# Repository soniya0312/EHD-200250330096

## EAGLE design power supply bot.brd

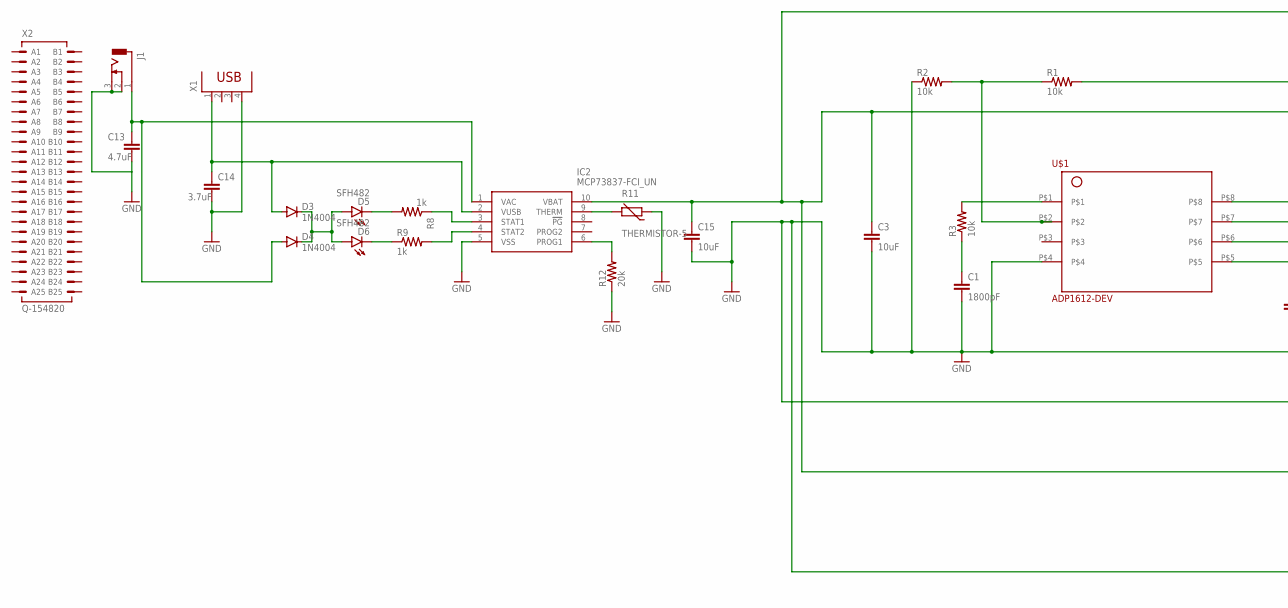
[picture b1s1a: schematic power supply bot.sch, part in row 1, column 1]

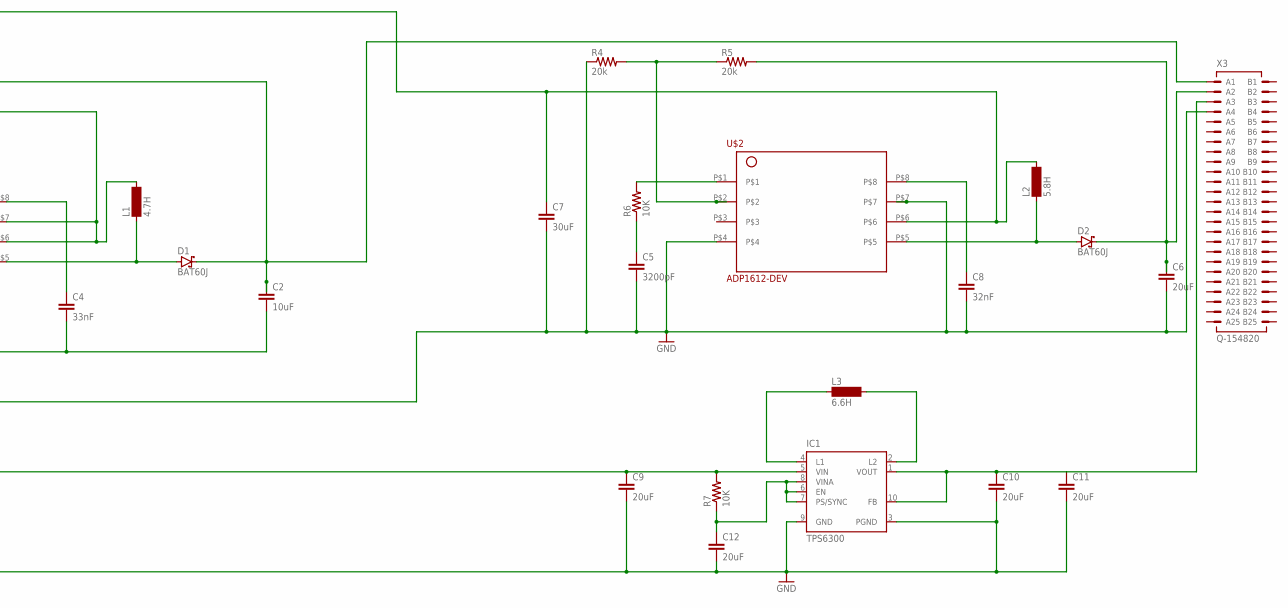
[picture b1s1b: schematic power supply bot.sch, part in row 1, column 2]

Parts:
C1: 1800pF; C2.5-4
C2, C3: 10uF; C2.5-4
C4: 33nF; C2.5-4
C5: 3200pF; C2.5-4
C6: 20uF; C2.5-4
C7: 30uF; C2.5-4
C8: 32nF; C2.5-4
C9, C10, C11, C12: 20uF; C2.5-3
C13: 4.7uF; C2.5-3
C14: 3.7uF; C2.5-3
C15: 10uF; C2.5-3
D1, D2: BAT60J; SOD323_ST
D3, D4: 1N4004; DO41-10
D5, D6: SFH482
IC1: TPS6300; DRC-S-PVSON-N10
IC2: MCP73837-FCI_UN; SOP50P490X110-10N
J1: DCJ0303
L1: 4.7H; BS11
L2: 5.8H; BS11
L3: 6.6H; BS75
R1, R2, R3: 10k; 0204/7
R4, R5: 20k; 0204/7
R6: 10K; 0204/7
R7: 10K; 0204/5
R8, R9: 1k; 0204/5
R11: THERMISTOR-5; R-5
R12: 20k; 0204/5
U$1, U$2: ADP1612-DEV; TQFP-ADP1612
X1: PN61729
X2, X3: Q-154820; 154820

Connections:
GND: C1.2, C2.2, C3.2, C4.2, C5.2, C6.2, C7.2, C8.2, C9.2, C10.2, C11.2, C12.2, C13.2, C14.1, C14.2, C15.2, D3.A, IC1.3 (PGND), IC1.9 (GND), IC2.2 (VUSB), IC2.5 (VSS), J1.2, J1.3, R2.1, R4.1, R11.1, R12.1, U$1.P$4, U$2.P$4, U$2.P$7, X1.1, X1.4, X3.A4
unnamed: R3.2, U$1.P$1
unnamed: C1.1, R3.1
unnamed: R1.1, R2.2, U$1.P$2
unnamed: C2.1, D1.C, R1.2, X3.A1
unnamed: D1.A, L1.1, U$1.P$5
unnamed: C4.1, U$1.P$8
unnamed: C3.1, C7.1, C9.1, C15.1, IC1.5 (VIN), IC2.10 (VBAT), L1.2, L2.2, R7.2, U$1.P$6, U$1.P$7, U$2.P$6
unnamed: R6.2, U$2.P$1
unnamed: C5.1, R6.1
unnamed: R4.2, R5.1, U$2.P$2
unnamed: C6.1, D2.C, R5.2, X3.A2
unnamed: C8.1, U$2.P$8
unnamed: D2.A, L2.1, U$2.P$5
unnamed: IC1.4 (L1), L3.1
unnamed: IC1.2 (L2), L3.2
unnamed: C10.1, C11.1, IC1.1 (VOUT), IC1.10 (FB), X3.A3
unnamed: IC2.9 (THERM), R11.2
unnamed: C12.1, IC1.6 (EN), IC1.7 (PS/SYNC), IC1.8 (VINA), R7.1
unnamed: IC2.6 (PROG1), R12.2
unnamed: D5.K (C), R8.2
unnamed: D6.K (C), R9.1
unnamed: C13.1, D4.A, IC2.1 (VAC), J1.1
unnamed: IC2.3 (STAT1), R8.1
unnamed: IC2.4 (STAT2), R9.2
unnamed: D3.C, D4.C, D5.A, D6.A

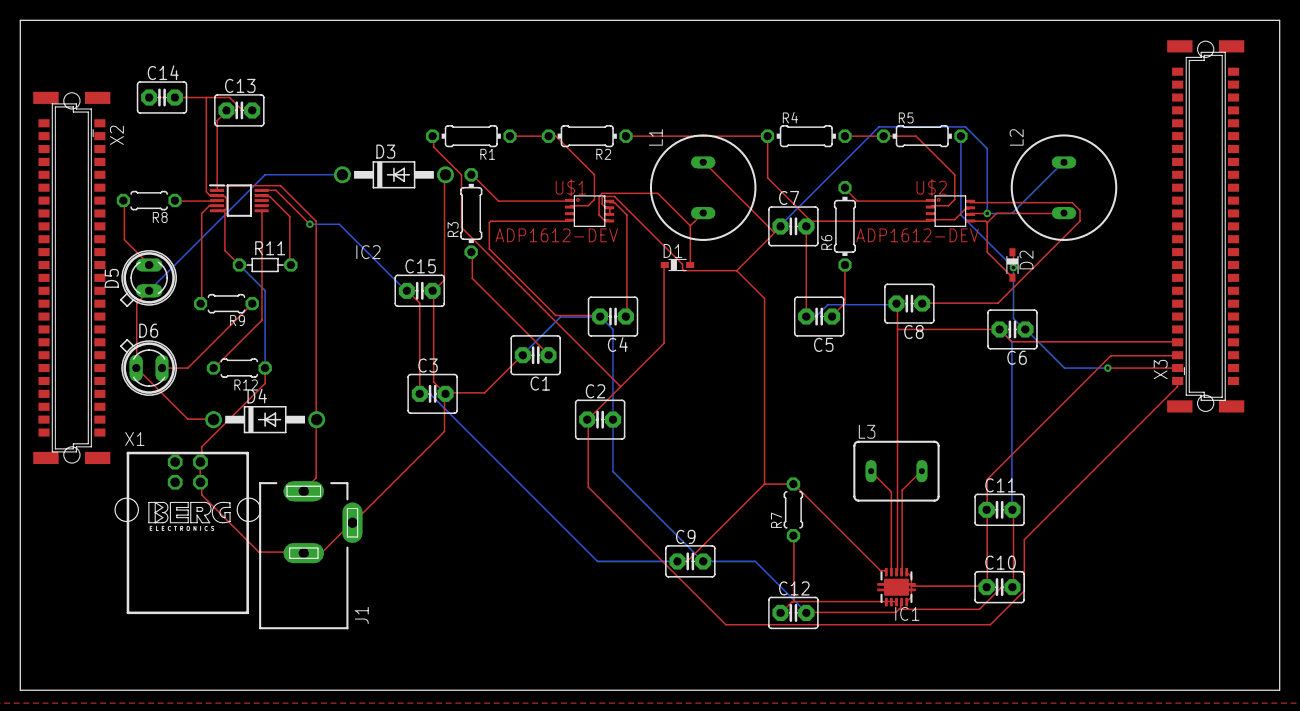
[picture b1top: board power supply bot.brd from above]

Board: 2 copper layers, 124.1 x 66.0 mm, 43 parts (0 on the bottom side), 26 nets.

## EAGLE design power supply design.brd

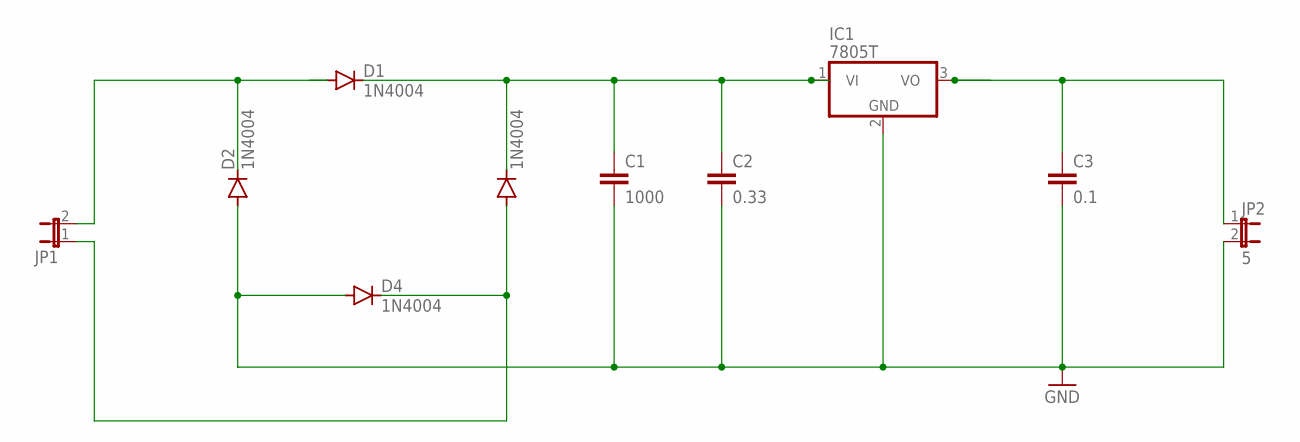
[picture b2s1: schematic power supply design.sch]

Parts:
C1: 1000; C2.5-3
C2: 0.33; C2.5-3
C3: 0.1; C2.5-3
D1, D2, D3, D4: 1N4004; DO41-10
IC1: 7805T; TO220H
JP1: 12; JP1
JP2: 5; JP1

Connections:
GND: C1.2, C2.2, C3.2, D2.A, D4.A, IC1.2 (GND), JP2.2
unnamed: C3.1, IC1.3 (VO), JP2.1
unnamed: C1.1, C2.1, D1.C, D3.C, IC1.1 (VI)
unnamed: D1.A, D2.C, JP1.2
unnamed: D3.A, D4.C, JP1.1

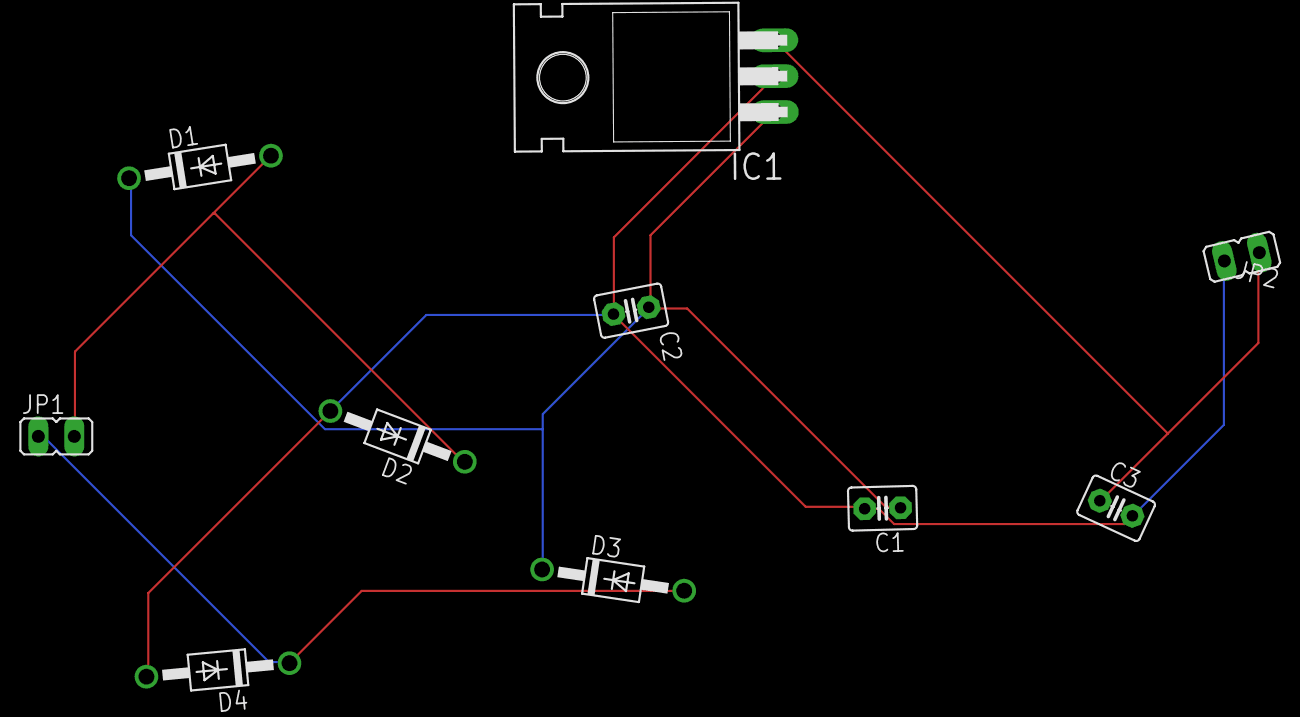
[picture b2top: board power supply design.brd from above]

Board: 2 copper layers, 10 parts (0 on the bottom side), 5 nets.

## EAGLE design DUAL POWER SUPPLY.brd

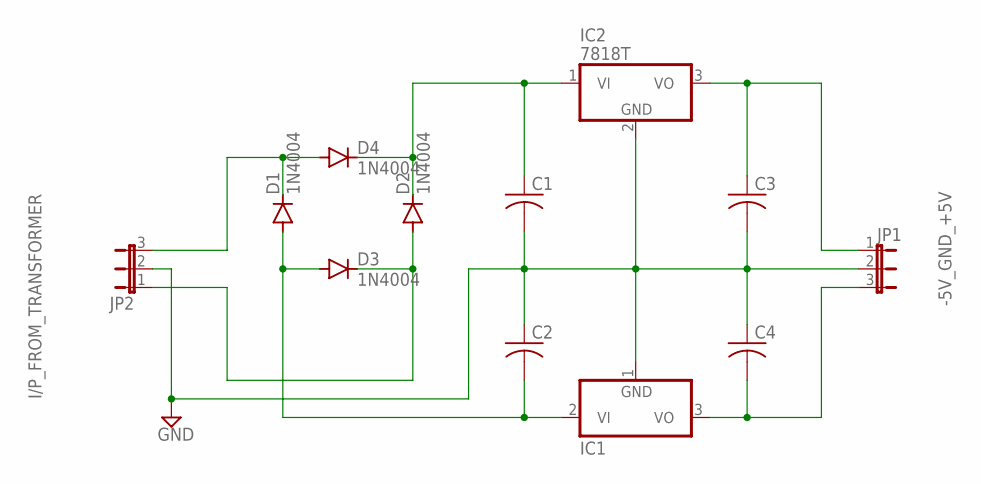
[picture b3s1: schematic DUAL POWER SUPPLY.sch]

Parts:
C1, C2, C3, C4: C-US025-024X044; C025-024X044
D1, D2, D3, D4: 1N4004; DO41-10
IC1: 79L05Z; TO92
IC2: 7818T; TO220H
JP1, JP2: JP2E; JP2

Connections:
GND: C1.2, C2.1, C3.2, C4.1, IC1.1 (GND), IC2.2 (GND), JP1.2, JP2.2
unnamed: D1.C, D4.A, JP2.3
unnamed: C1.1, D2.C, D4.C, IC2.1 (VI)
unnamed: D2.A, D3.C, JP2.1
unnamed: C2.2, D1.A, D3.A, IC1.2 (VI)
unnamed: C3.1, IC2.3 (VO), JP1.1
unnamed: C4.2, IC1.3 (VO), JP1.3

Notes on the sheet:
I/P_FROM_TRANSFORMER
-5V_GND_+5V

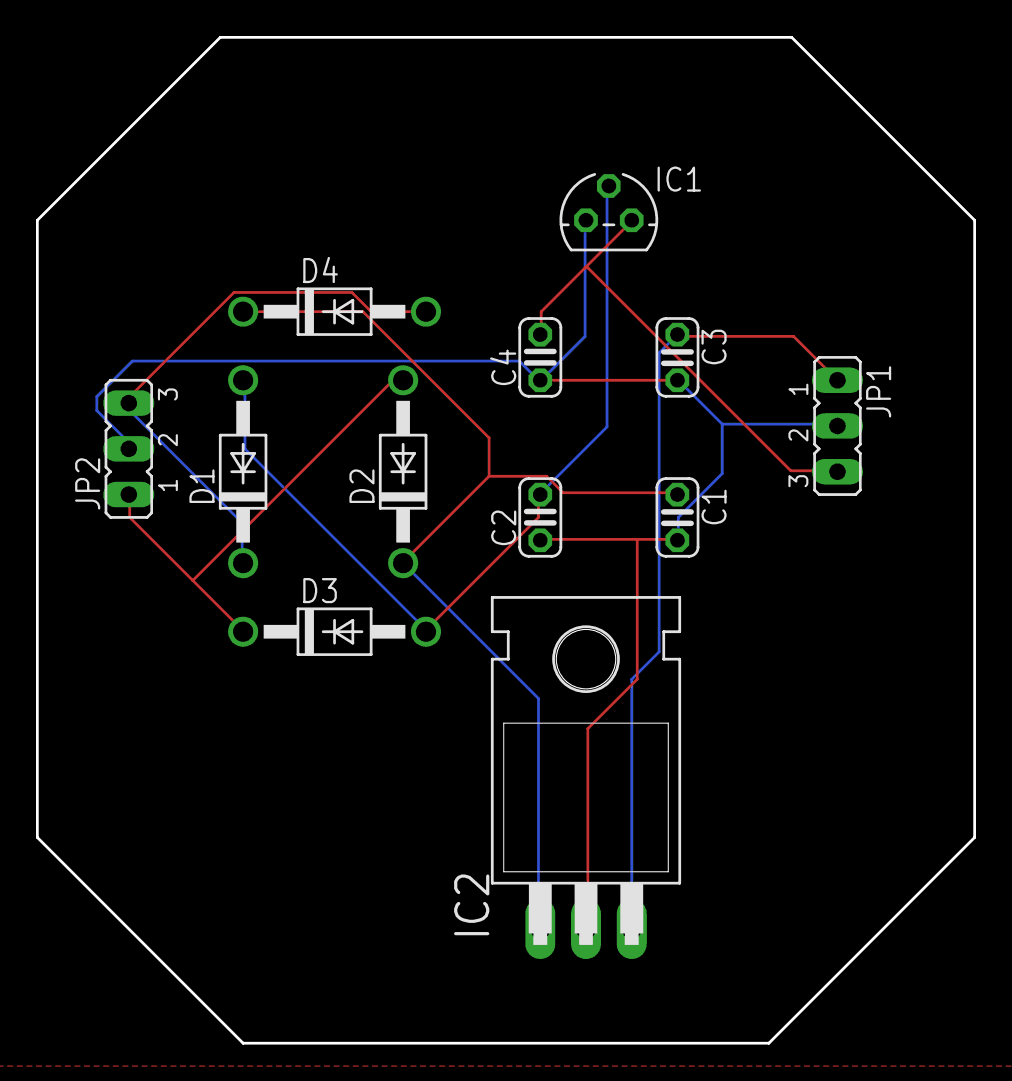
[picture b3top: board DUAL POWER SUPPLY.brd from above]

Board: 2 copper layers, 52.1 x 55.9 mm, 12 parts (0 on the bottom side), 7 nets.

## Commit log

2020-10-01 Create Assignment
